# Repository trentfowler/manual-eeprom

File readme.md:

# Manual EEPROM programmer

**Description:** KiCad project files for manual EEPROM programmer pcb that uses dip switches to program the the AT28C16 EEPROM

AT28C16 - http://cva.stanford.edu/classes/cs99s/datasheets/at28c16.pdf

**Rev 1 final:**

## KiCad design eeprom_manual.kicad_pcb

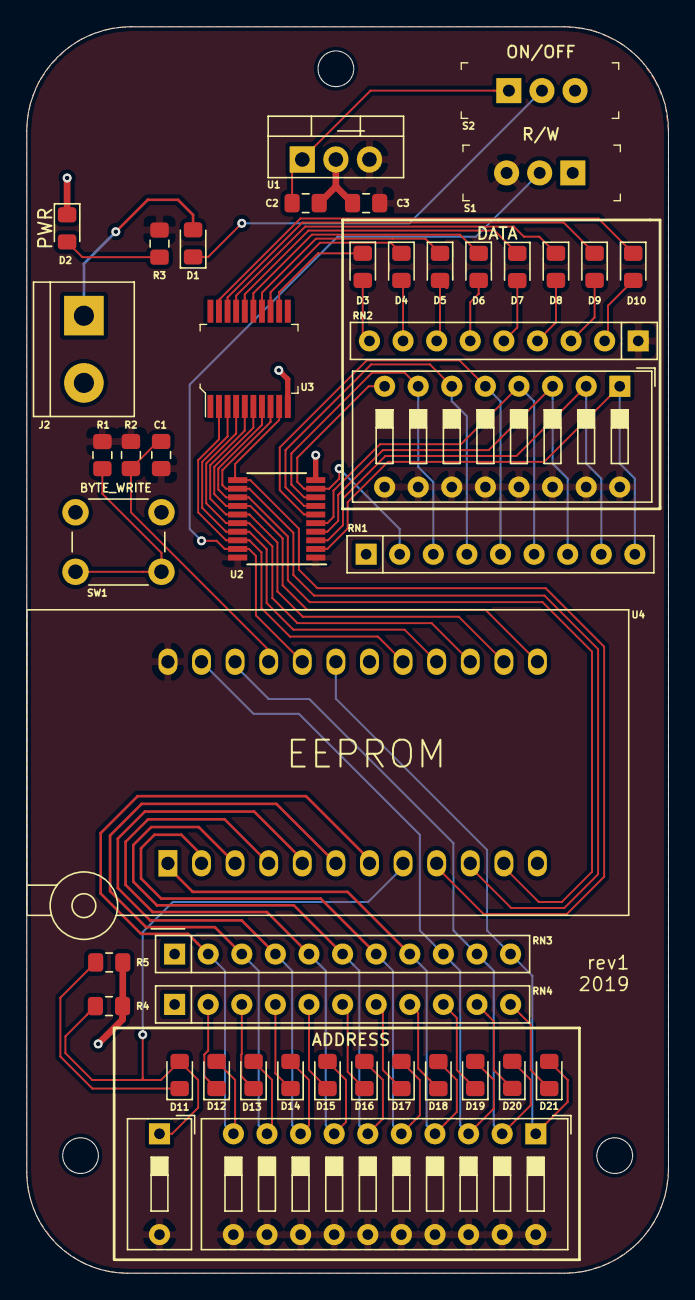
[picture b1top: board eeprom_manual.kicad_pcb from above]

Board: 2 copper layers, 48.5 x 94.2 mm, 44 parts (0 on the bottom side), 63 nets.

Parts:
C1: 10nF; C_0805_2012Metric_Pad1.15x1.40mm_HandSolder
C2: .33uF; C_0805_2012Metric_Pad1.15x1.40mm_HandSolder
C3: .1uF; C_0805_2012Metric_Pad1.15x1.40mm_HandSolder
D1: D; D_0805_2012Metric_Pad1.15x1.40mm_HandSolder
D2: D2; LED_0805_2012Metric_Pad1.15x1.40mm_HandSolder
D3, D4, D5, D6, D7, D8, D9, D10, D11, D12, D13, D14, D15, D16, D17, D18, D19, D20, D21: RED; LED_0805_2012Metric_Pad1.15x1.40mm_HandSolder
J2: Conn_01x02; TerminalBlock_bornier-2_P5.08mm
R1, R4: 10k; R_0805_2012Metric_Pad1.15x1.40mm_HandSolder
R2: 680; R_0805_2012Metric_Pad1.15x1.40mm_HandSolder
R3: R_US; R_0805_2012Metric_Pad1.15x1.40mm_HandSolder
R5: 220; R_0805_2012Metric_Pad1.15x1.40mm_HandSolder
RN1: R_VALUE; R_Array_SIP9
RN2: 220; R_Array_SIP9
RN3: 10k; R_Array_SIP11
RN4: 220; R_Array_SIP11
S1: READ/WRITE; Switch_Slide_11.6x4mm_EG1218
S2: ON/OFF; Switch_Slide_11.6x4mm_EG1218
SW1: SW_SPST; SW_PUSH_6mm
SW2: SW_DIP_x08; SW_DIP_SPSTx08_Slide_9.78x22.5mm_W7.62mm_P2.54mm
SW3: SW_DIP_x10; SW_DIP_SPSTx10_Slide_9.78x27.58mm_W7.62mm_P2.54mm
SW4: SW_DIP_x01; SW_DIP_SPSTx01_Slide_9.78x4.72mm_W7.62mm_P2.54mm
U1: L7805; TO-220-3_Vertical
U2: 74HC245; TSSOP-20_4.4x6.5mm_P0.65mm
U3: M54513FP; SSOP-20_W5.3mm
U4: 28C16; DIP_Socket-24_W11.9_W12.7_W15.24_W17.78_W18.5_3M_224-1275-0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

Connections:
+5V: C1.1, C3.1, R1.2, R2.2, R3.1, RN2.1, S1.3, SW2.9, SW2.10, SW2.11, SW2.12, SW2.13, SW2.14, SW2.15, SW2.16, SW3.11, SW3.12, SW3.13, SW3.14, SW3.15, SW3.16, SW3.17, SW3.18, SW3.19, SW3.20, SW4.2, U1.3, U2.1, U2.20, U4.24
GND: C2.2, C3.2, D2.1, J2.2, R4.1, R5.1, RN1.1, RN3.1, RN4.1, S1.1, SW1.1, U1.2, U2.10, U3.10, U4.12, U4.18
unnamed: C2.1, S2.1, U1.1
unnamed: D1.1, S2.2
unnamed: D1.2, J2.1
unnamed: D2.2, R3.2
unnamed: D3.1, U3.12
unnamed: D3.2, RN2.9
unnamed: D4.1, U3.13
unnamed: D4.2, RN2.8
unnamed: D5.1, U3.14
unnamed: D5.2, RN2.7
unnamed: D6.1, U3.15
unnamed: D6.2, RN2.6
unnamed: D7.1, U3.16
unnamed: D7.2, RN2.5
unnamed: D8.1, U3.17
unnamed: D8.2, RN2.4
unnamed: D9.1, U3.18
unnamed: D9.2, RN2.3
unnamed: D10.1, U3.19
unnamed: D10.2, RN2.2
unnamed: D11.1, R5.2
unnamed: D11.2, R4.2, SW4.1, U4.8
unnamed: D12.1, RN4.2
unnamed: D12.2, RN3.2, SW3.10, U4.7
unnamed: D13.1, RN4.3
unnamed: D13.2, RN3.3, SW3.9, U4.6
unnamed: D14.1, RN4.4
unnamed: D14.2, RN3.4, SW3.8, U4.5
unnamed: D15.1, RN4.5
unnamed: D15.2, RN3.5, SW3.7, U4.4
unnamed: D16.1, RN4.6
unnamed: D16.2, RN3.6, SW3.6, U4.3
unnamed: D17.1, RN4.7
unnamed: D17.2, RN3.7, SW3.5, U4.2
unnamed: D18.1, RN4.8
unnamed: D18.2, RN3.8, SW3.4, U4.1
unnamed: D19.1, RN4.9
unnamed: D19.2, RN3.9, SW3.3, U4.23
unnamed: D20.1, RN4.10
unnamed: D20.2, RN3.10, SW3.2, U4.22
unnamed: D21.1, RN4.11
unnamed: D21.2, RN3.11, SW3.1, U4.19
unnamed: R1.1, SW1.2
unnamed: RN1.2, SW2.8, U2.9
unnamed: RN1.3, SW2.7, U2.8
unnamed: RN1.4, SW2.6, U2.7
unnamed: RN1.5, SW2.5, U2.6
unnamed: RN1.6, SW2.4, U2.5
unnamed: RN1.7, SW2.3, U2.4
unnamed: RN1.8, SW2.2, U2.3
unnamed: RN1.9, SW2.1, U2.2
unnamed: U2.11, U3.9, U4.9
unnamed: U2.12, U3.8, U4.10
unnamed: U2.13, U3.7, U4.11
unnamed: U2.14, U3.6, U4.13
unnamed: U2.15, U3.5, U4.14
unnamed: U2.16, U3.4, U4.15
unnamed: U2.17, U3.3, U4.16
unnamed: U2.18, U3.2, U4.17
OE: S1.2, U2.19, U4.20
WR: C1.2, R2.1, U4.21

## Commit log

2019-09-09 Assign footprints (initial)
2019-09-09 Update footprints
    - Generate net list
2019-09-10 Created pcbnew component layout
2019-09-10 Added traces to pcb
    - pcbnew component layout adjustments
2019-09-10 Add images
    - Update readme
2019-09-11 Add silkscreen labels, Clean up traces
2019-09-11 rev.1 final (add silkscreen, gerbers, spread traces)
    - Generated gerbers and drill file
    - custom bitmap logo created, assigned component footprint, placed on back
    of pcb
    - Updated readme with rev.1 final pictures
    - Spread out traces and tweaked clearances
2019-09-11 Remove old schematic
2019-09-11 Update readme resolve dead link
2019-09-11 Update readme fix dead link
2019-09-11 Sync kicad working files with project after program save/exit
2019-09-11 Added footprint for S8211R coin cell batt
2019-09-11 Added SC70-5 and SOT-23-5 footprints
    - Clean up unused footprint
2019-09-11 move from lm7805 to coin cell with boost converter +5v wall supply
    - reorg single sheet sch to hierarchial kicad layout
2019-09-11 Rename +5v global flags as 5V_SHARED
    - moved 1x dip switch from place A0 to A10
